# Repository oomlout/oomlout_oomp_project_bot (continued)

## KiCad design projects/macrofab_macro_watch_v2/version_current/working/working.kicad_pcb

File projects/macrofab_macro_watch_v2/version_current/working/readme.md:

# Macro_Watch_V2 by MacroFab  
This is a harvested standardized copy of a project from github.  
The original project can be found at:  
https://github.com/MacroFab/Macro_Watch_V2  
Please consult that link for additional, details, files, and license information.  
Note: It was auto harvested and if the original repo had more than one board file or anything out of the ordinary the files here are likely not representative.

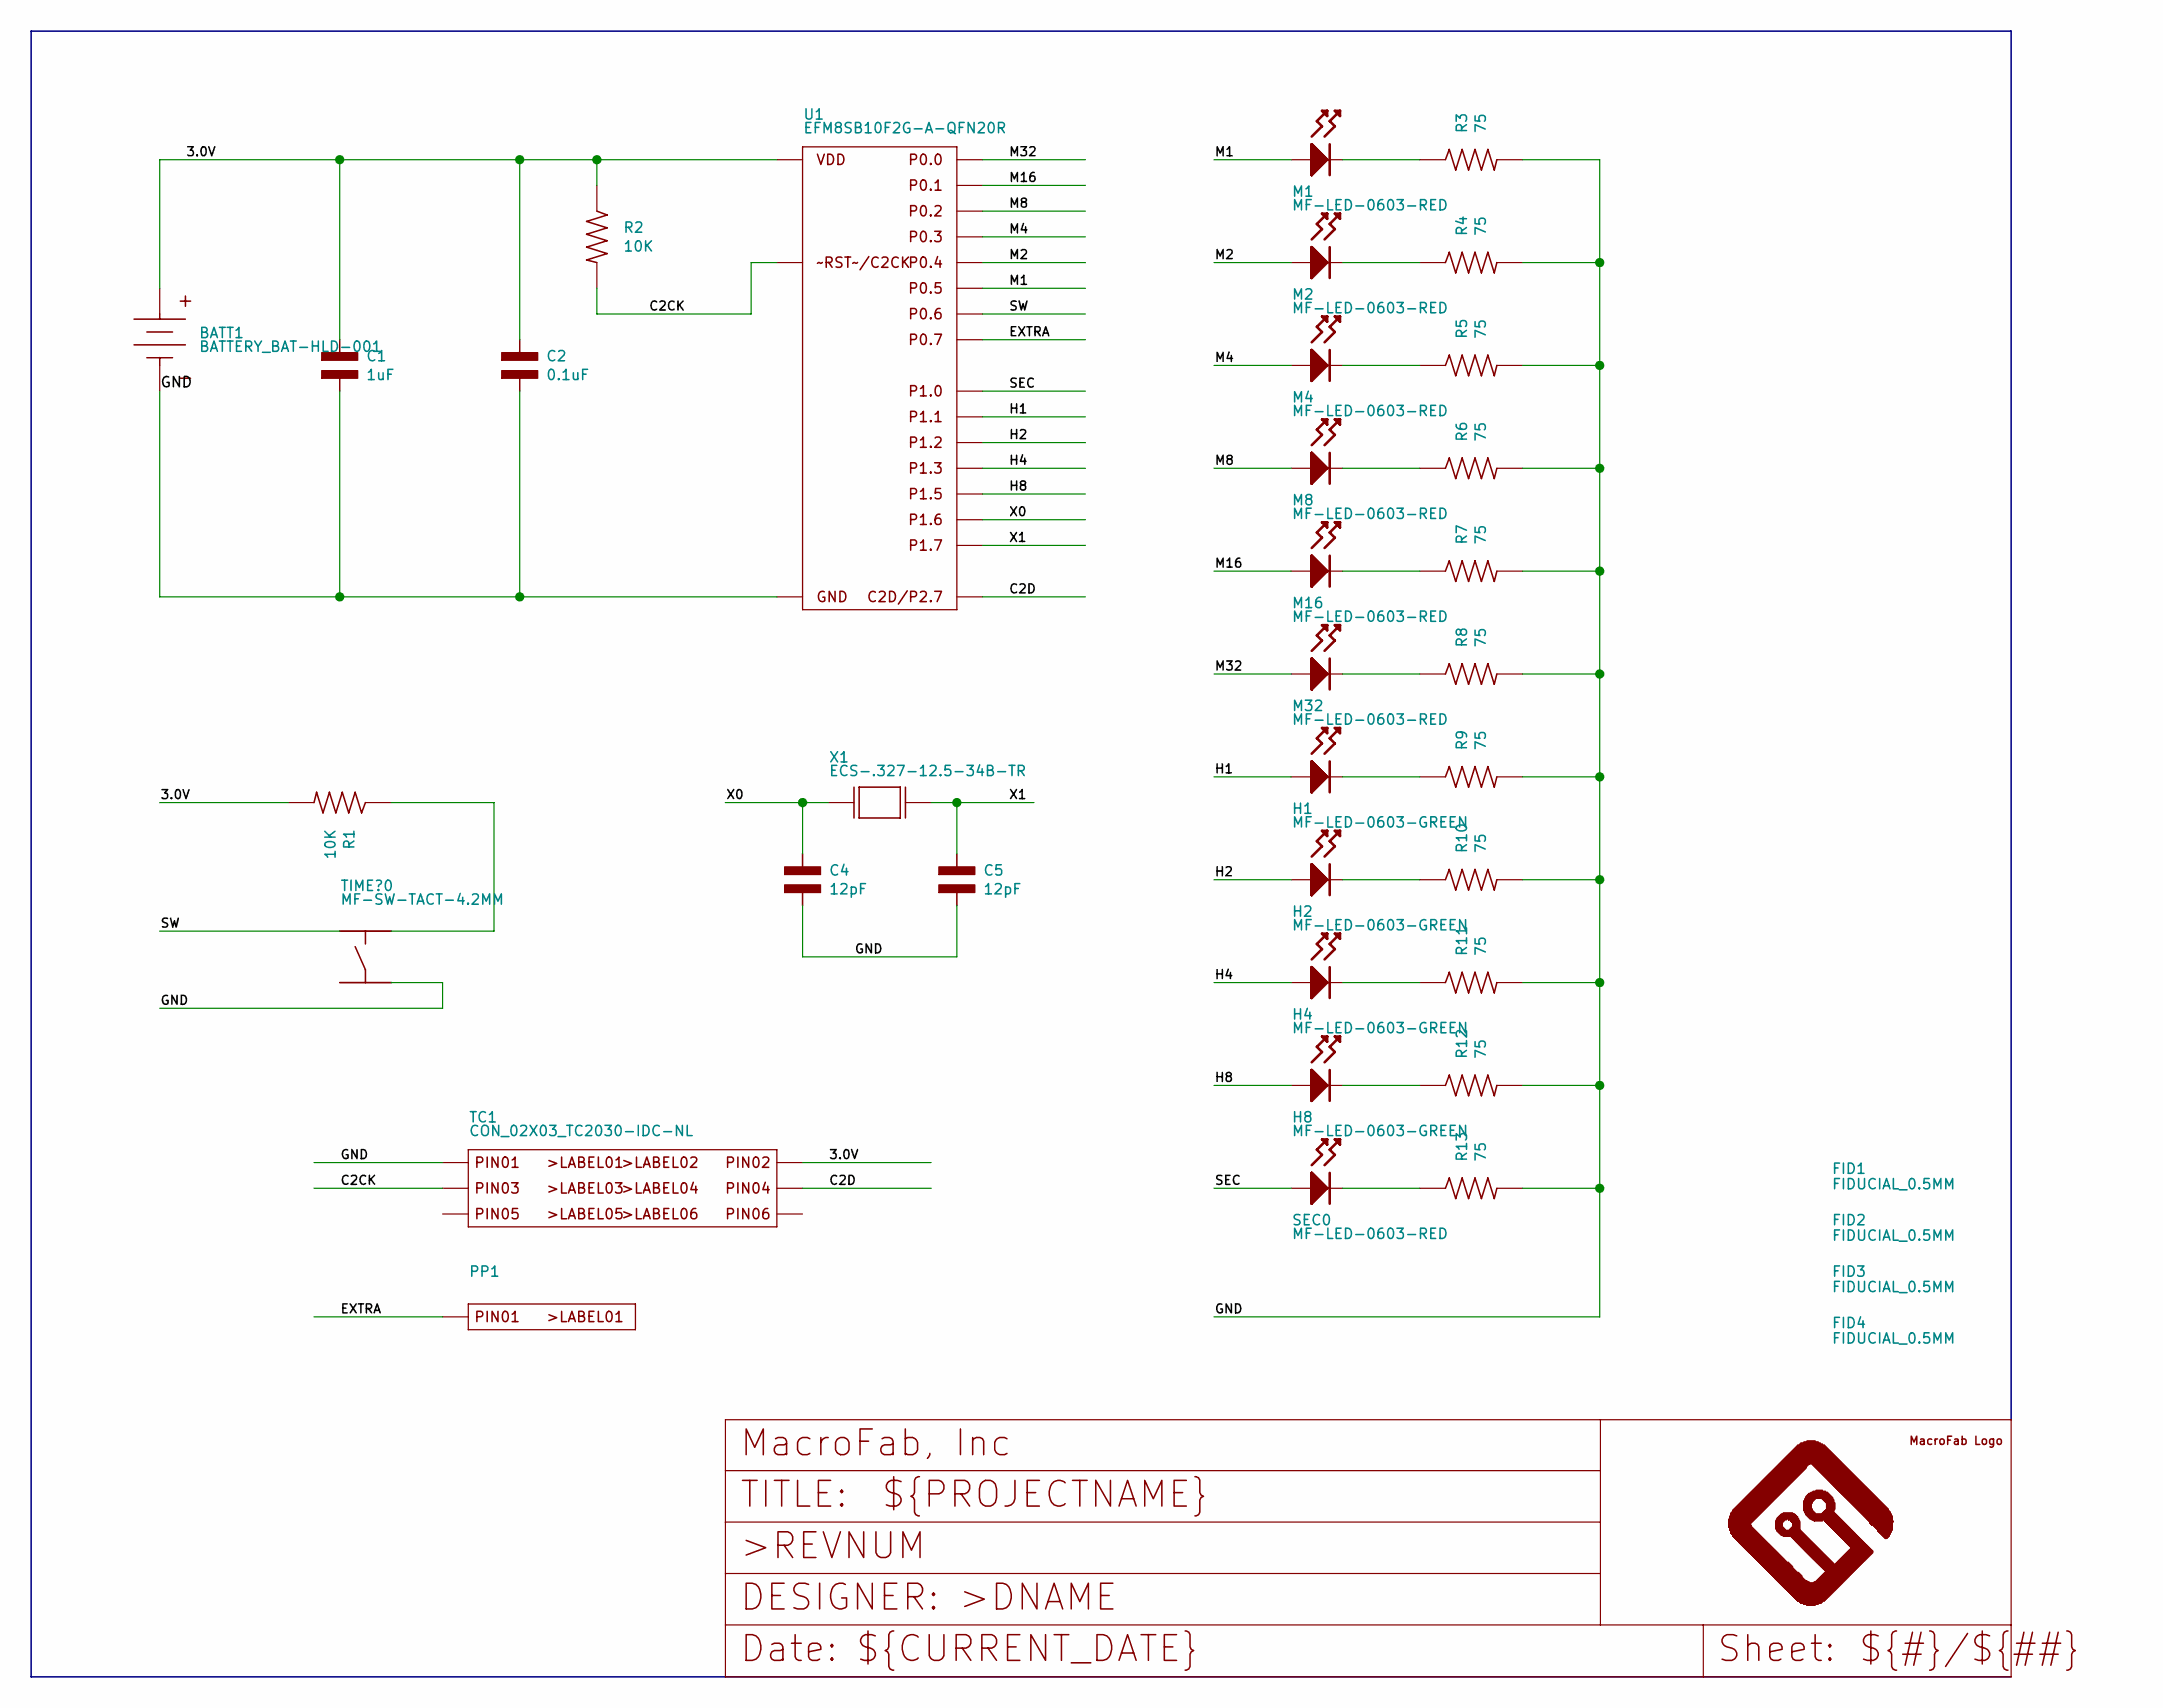
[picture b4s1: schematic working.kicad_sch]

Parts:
BATT1: BATTERY_BAT-HLD-001; BAT-HLD-001
C1: 1uF; C0402; MPN MF-CAP-0402-1uF
C2: 0.1uF; C0402; MPN MF-CAP-0402-0.1uF
C4, C5: 12pF; C0402; MPN 500R07S120KV4T
FID1, FID2, FID3, FID4: FIDUCIAL_0.5MM
FRAME1: MF_FRAMEDEFAULT; MF_FRAME_DEFAULT
H1, H2, H4, H8: MF-LED-0603-GREEN; LED0603
M1, M2, M4, M8, M16, M32: MF-LED-0603-RED; LED0603
PP1: POGO_PIN_01X01_70-9150; POGO_PIN_70-9150
R1, R2: 10K; R0402; MPN MF-RES-0402-10K
R3, R4, R5, R6, R7, R8, R9, R10, R11, R12, R13: 75; R0402; MPN MF-RES-0402-75
SEC0: MF-LED-0603-RED; LED0603
TC1: CON_02X03_TC2030-IDC-NL; TC2030-IDC-NL
TIME?0: MF-SW-TACT-4.2MM; TACT4.2MM
U1: EFM8SB10F2G-A-QFN20R; EFM8SB10F(2_4_8)G-A-QFN20; MPN EFM8SB10F2G-A-QFN20R
U$1: MF_LOGOLOGO_SMALL; MF_LOGO_SMALL
X1: ECS-.327-12.5-34B-TR; ECX-31B_SERIES; MPN ECS-.327-12.5-34B-TR

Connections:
3.0V: BATT1.POS_0 (POS), BATT1.POS_1 (POS), C1.P$1, C2.P$1, R1.P$2, R2.P$1, TC1.P$2 (PIN2), U1.P$4 (VDD)
C2CK: R2.P$2, TC1.P$3 (PIN3), U1.P$5 (~RST/C2CK)
C2D: TC1.P$4 (PIN4), U1.P$6 (C2D/P2.7)
EXTRA: PP1.P$1, U1.P$15 (P0.7)
GND: BATT1.NEG_0 (NEG), C1.P$2, C2.P$2, C4.P$2, C5.P$2, R3.P$2, R4.P$2, R5.P$2, R6.P$2, R7.P$2, R8.P$2, R9.P$2, R10.P$2, R11.P$2, R12.P$2, R13.P$2, TC1.P$1 (PIN1), TIME?0.P$4, U1.P$3 (GND), U1.P$12 (GND), U1.PAD (GND)
H1: H1.ANODE, U1.P$13 (P1.1)
H2: H2.ANODE, U1.P$11 (P1.2)
H4: H4.ANODE, U1.P$10 (P1.3)
H8: H8.ANODE, U1.P$9 (P1.5)
M1: M1.ANODE, U1.P$17 (P0.5)
M2: M2.ANODE, U1.P$18 (P0.4)
M4: M4.ANODE, U1.P$19 (P0.3)
M8: M8.ANODE, U1.P$20 (P0.2)
M16: M16.ANODE, U1.P$1 (P0.1)
M32: M32.ANODE, U1.P$2 (P0.0)
unnamed: R1.P$1, TIME?0.P$2
unnamed: M1.CATHODE, R3.P$1
unnamed: M2.CATHODE, R4.P$1
unnamed: M4.CATHODE, R5.P$1
unnamed: M8.CATHODE, R6.P$1
unnamed: M16.CATHODE, R7.P$1
unnamed: M32.CATHODE, R8.P$1
unnamed: H1.CATHODE, R9.P$1
unnamed: H2.CATHODE, R10.P$1
unnamed: H4.CATHODE, R11.P$1
unnamed: H8.CATHODE, R12.P$1
unnamed: R13.P$1, SEC0.CATHODE
SEC: SEC0.ANODE, U1.P$14 (P1.0)
SW: TIME?0.P$1, U1.P$16 (P0.6)
X0: C4.P$1, U1.P$8 (P1.6), X1.P$1 (X0)
X1: C5.P$1, U1.P$7 (P1.7), X1.P$2 (X1)

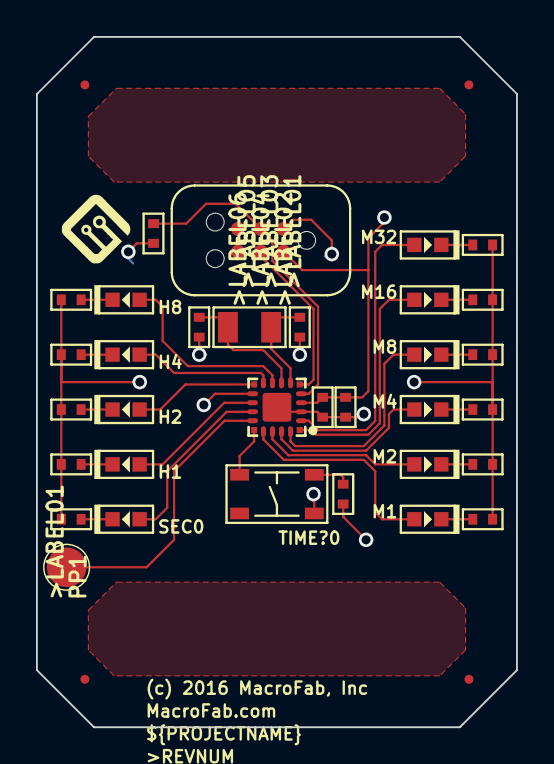
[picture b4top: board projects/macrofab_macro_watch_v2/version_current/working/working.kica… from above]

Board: 2 copper layers, 26.7 x 38.4 mm, 40 parts (1 on the bottom side), 31 nets.

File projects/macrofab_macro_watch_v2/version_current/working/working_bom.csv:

"Id";"Designator";"Footprint";"Quantity";"Designation";"Supplier and ref";
1;"U$1";"MF_LOGO_SMALL";1;"MF_LOGOLOGO_SMALL";;;
2;"R10,R11,R7,R12,R6,R8,R13,R5,R3,R9,R4";"R0402";11;"75";;;
3;"U1";"EFM8SB10F(2_4_8)G-A-QFN20";1;"EFM8SB10F2G-A-QFN20R";;;
4;"FRAME1";"MF_FRAME_DEFAULT";1;"";;;
5;"H8,H2,H4,H1";"LED0603";4;"MF-LED-0603-GREEN";;;
6;"C2";"C0402";1;"0.1uF";;;
7;"C1";"C0402";1;"1uF";;;
8;"M32,SEC0,M16,M8,M4,M1,M2";"LED0603";7;"MF-LED-0603-RED";;;
9;"FID1,FID3,FID2,FID4";"FIDUCIAL_0.5MM";4;"";;;
10;"R1,R2";"R0402";2;"10K";;;
11;"C4,C5";"C0402";2;"12pF";;;
12;"X1";"ECX-31B_SERIES";1;"ECS-.327-12.5-34B-TR";;;
13;"TC1";"TC2030-IDC-NL";1;"TC2030-IDC-NL";;;
14;"PP1";"POGO_PIN_70-9150";1;"";;;
15;"TIME?0";"TACT4.2MM";1;"MF-SW-TACT-4.2MM";;;
16;"BATT1";"BAT-HLD-001";1;"BAT-HLD-001";;;

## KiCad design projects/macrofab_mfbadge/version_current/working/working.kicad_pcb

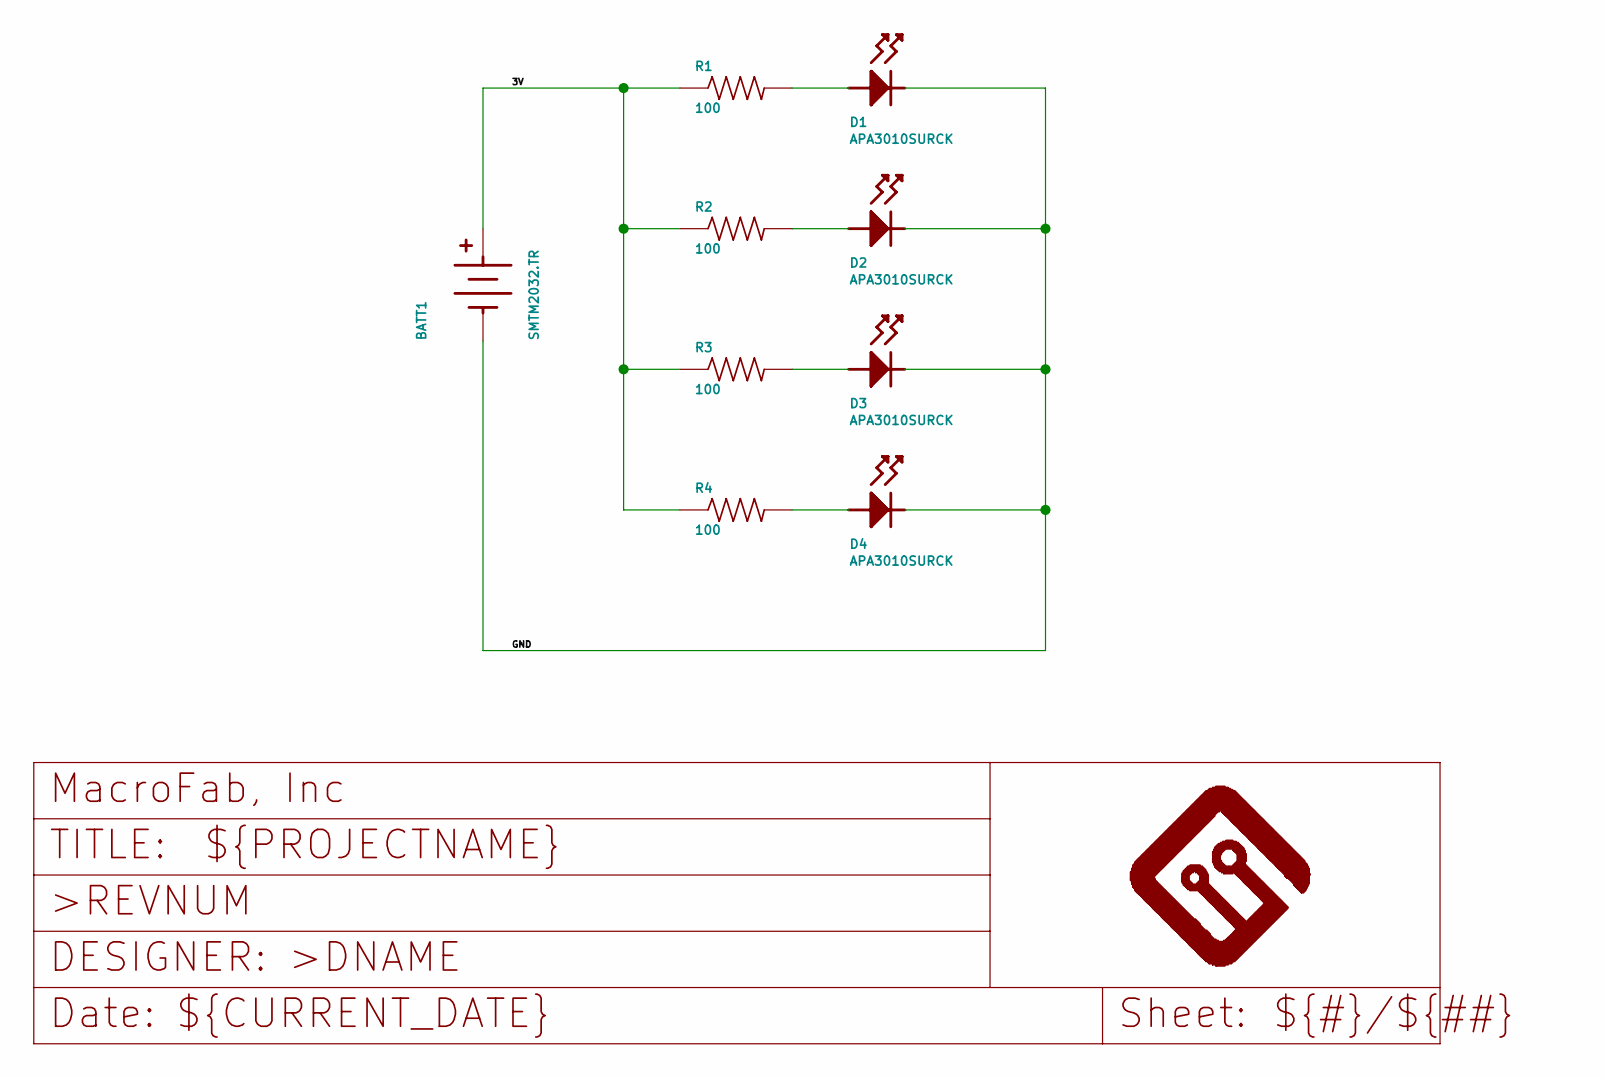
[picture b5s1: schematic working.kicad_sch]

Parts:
BATT1: SMTM2032.TR; SMTM2032
D1, D2, D3, D4: APA3010SURCK; APA3010
R1, R2, R3, R4: 100; 0805
U$1: MF_FRAMEMF_FRAME; MF_FRAME

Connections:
3V: BATT1.BATT- (-), D1.1 (CATHODE), D2.1 (CATHODE), D3.1 (CATHODE), D4.1 (CATHODE)
unnamed: D1.2 (ANODE), R1.2
unnamed: D2.2 (ANODE), R2.2
unnamed: D3.2 (ANODE), R3.2
unnamed: D4.2 (ANODE), R4.2
unnamed: BATT1.BATT+_0 (+), BATT1.BATT+_1 (+), R1.1, R2.1, R3.1, R4.1

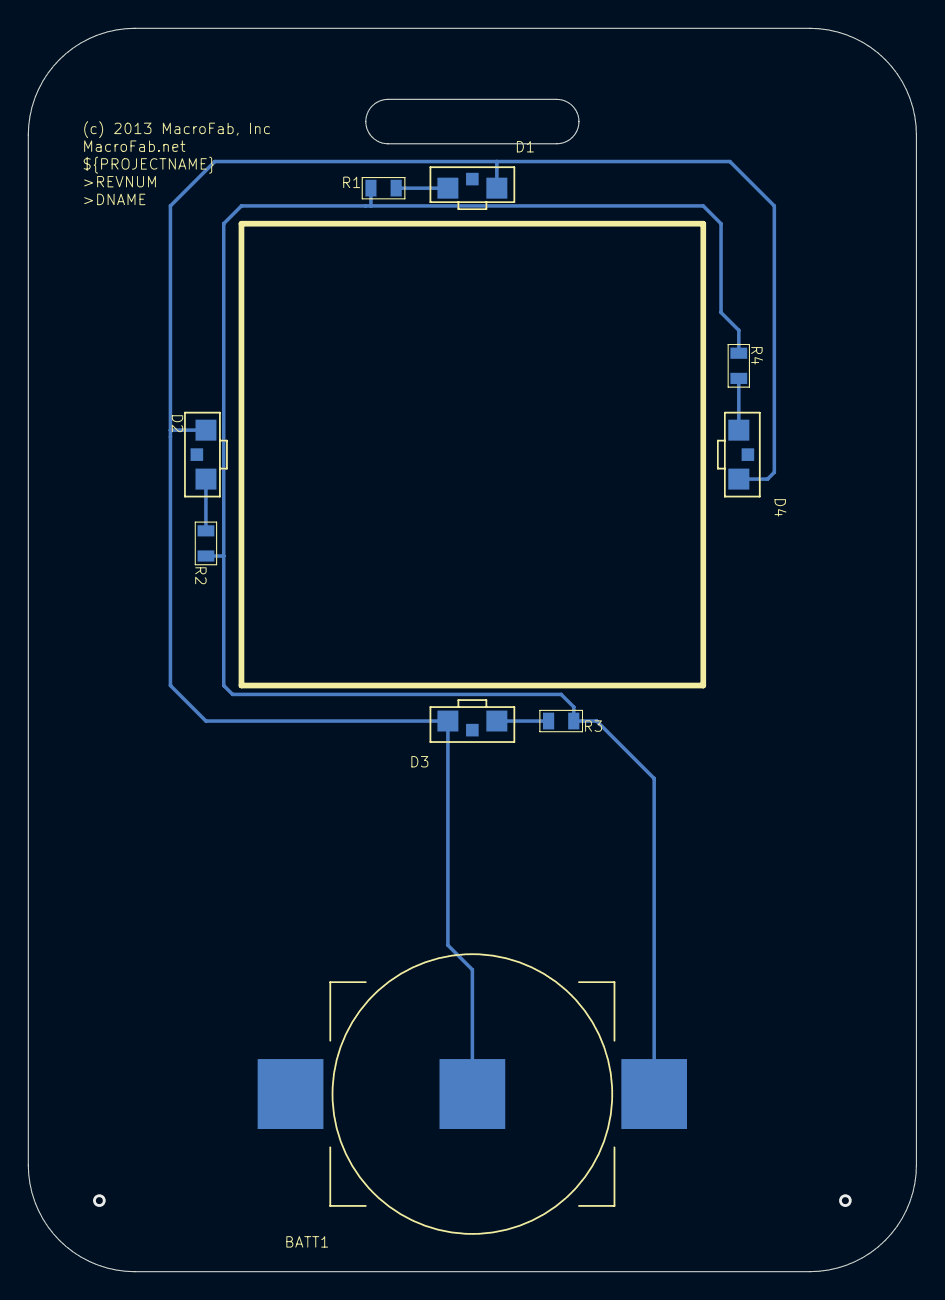
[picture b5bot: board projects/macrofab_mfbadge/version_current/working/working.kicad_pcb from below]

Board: 2 copper layers, 63.5 x 88.9 mm, 10 parts (10 on the bottom side), 6 nets.

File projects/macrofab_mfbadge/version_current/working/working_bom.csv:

"Id";"Designator";"Footprint";"Quantity";"Designation";"Supplier and ref";
1;"D2,D3,D1,D4";"APA3010";4;"APA3010SURCK";;;
2;"R1,R4,R3,R2";"0805";4;"100";;;
3;"U$1";"MF_FRAME";1;"MF_FRAMEMF_FRAME";;;
4;"BATT1";"SMTM2032";1;"SMTM2032.TR";;;

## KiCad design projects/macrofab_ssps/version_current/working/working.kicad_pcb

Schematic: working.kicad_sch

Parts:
C1, C6, C7, C8, C9, C10, C11, C24, C25, C26: 0.1uF; 0603
C2, C3, C4, C5: MF-CAP-6.3MM-100uF; 6.3MM_CAP_SMD
C12, C13: 47pF; C0603
C14, C15: 0.1uF; C0603
C16: 4.7uF; CP4MM
C17, C18, C19, C20, C21, C22, C23: .1uF; 0603
D1, D2, D3, D4, D5, D6: WP1043ID; WP1043
D7, D8, D9, D10, D11, D12: WP1043YD; WP1043
D13, D14, D15, D16, D17, D18, D19, D20, D21, D22, D23, D24, D25, D26, D27: WP1043GD; WP1043
DISP1, DISP2, DISP3, DISP4, DISP5: PSA08-11SRWA
EN1: PEL12T-4226F-S1024; PEL12T
FID1, FID2: FIDUCIAL_100MIL
FRAME1: MF_FRAMEDEFAULT; MF_FRAME_DEFAULT
GND0: 5001; KEYSTONE_5115-5119
J1: 61400413321
J2: CON_01X08_2.54MM_PIN_HEADER; 2.54MM_01X08_PIN_HEADER
L1: MI0603K300R-10; L0603
LCD1: CU16025-UW6J
R1, R2, R3, R4, R5, R6, R7, R15: 1K; 0603
R8, R9: 27; R0603
R10: 10K; R0603
R11: 4.7K; R0603
R12, R13, R14, R16, R17, R18, R19, R20, R21, R22: 10K; 0603
SW1, SW2: B3W-9000-RG2C; B3W-9000
SW3: 5501M112; 5501
U1: P8X32A-M44; P8X32A_QFN-44
U2, U3, U4, U5, U6, U9, U10, U14: STP16CP05XTTR; STP16CP05XTTR_TTSOP-24
U7: AP1084D25G-13; AP1084_TO-252-3L
U8: AP1084D33G-13; AP1084_TO-252-3L
U11: CAT24C512WI-GT3; SOIC-8_W
U12: IP4234CZ6; IP4234CZ6_SOT-457-6
U13: FT234XD-R; FT234X_DFN-12
UNK5V0: 5000; KEYSTONE_5115-5119
X1: ABMM-6.000MHZ-B2-T; 7MMX5MM

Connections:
2.5V: C3.POS, D1.A (ANODE), D2.A (ANODE), D3.A (ANODE), D4.A (ANODE), D5.A (ANODE), D6.A (ANODE), D7.A (ANODE), D8.A (ANODE), D9.A (ANODE), D10.A (ANODE), D11.A (ANODE), D12.A (ANODE), D13.A (ANODE), D14.A (ANODE), D15.A (ANODE), D16.A (ANODE), D17.A (ANODE), D18.A (ANODE), D19.A (ANODE), D20.A (ANODE), D21.A (ANODE), D22.A (ANODE), D23.A (ANODE), D24.A (ANODE), D25.A (ANODE), D26.A (ANODE), D27.A (ANODE), DISP1.P$11 (COM), DISP2.P$11 (COM), DISP3.P$11 (COM), DISP4.P$11 (COM), DISP5.P$11 (COM), SW1.ANODE_1, SW1.ANODE_2, SW2.ANODE_1, SW2.ANODE_2, SW3.ANODE_1, SW3.ANODE_2, U7.3 (OUT)
3.3V: C1.1, C5.POS, C6.1, C7.1, C8.1, C9.1, C10.1, C11.1, C15.P$1, C16.P$1, C17.2, C18.2, C19.2, C20.2, C22.2, C23.2, C24.1, EN1.5, R12.2, R13.2, R14.2, R16.2, R17.2, R20.1, R21.1, R22.1, U1.8 (VDD), U1.18 (VDD), U1.30 (VDD), U1.40 (VDD), U2.P$24 (VDD), U3.P$24 (VDD), U4.P$24 (VDD), U5.P$24 (VDD), U6.P$24 (VDD), U8.3 (OUT), U9.P$24 (VDD), U10.P$24 (VDD), U11.8 (VCC), U13.4 (VCC), U14.P$24 (VDD)
3V3OUT: C14.P$1, U13.2 (RESET#), U13.3 (3V3OUT), U13.9 (VCCIO)
D+_USB: J1.3 (D+), U12.1 (I/O1A)
D-_USB: J1.2 (D-), U12.6 (I/O2A)
DISP1_A: DISP1.P$1 (A), U2.P$20 (~OUT15)
DISP1_B: DISP1.P$18 (B), U2.P$5 (~OUT0)
DISP1_C: DISP1.P$16 (C), U2.P$7 (~OUT2)
DISP1_D: DISP1.P$13 (D), U2.P$10 (~OUT5)
DISP1_DATA: U1.2 (P5), U2.P$2 (SDI)
DISP1_DP: DISP1.P$12 (DP), U10.P$9 (~OUT4)
DISP1_E: DISP1.P$10 (E), U2.P$11 (~OUT6)
DISP1_F: DISP1.P$9 (F), U2.P$12 (~OUT7)
DISP1_G: DISP1.P$8 (G), U2.P$13 (~OUT8)
DISP1_H: DISP1.P$4 (H), U2.P$17 (~OUT12)
DISP1_K: DISP1.P$3 (K), U2.P$18 (~OUT13)
DISP1_M: DISP1.P$2 (M), U2.P$19 (~OUT14)
DISP1_N: DISP1.P$17 (N), U2.P$6 (~OUT1)
DISP1_P: DISP1.P$15, U2.P$8 (~OUT3)
DISP1_R: DISP1.P$14 (R), U2.P$9 (~OUT4)
DISP1_S: DISP1.P$6 (S), U2.P$15 (~OUT10)
DISP1_T: DISP1.P$7 (T), U2.P$14 (~OUT9)
DISP1_U: DISP1.P$5 (U), U2.P$16 (~OUT11)
DISP2_A: DISP2.P$1 (A), U3.P$20 (~OUT15)
DISP2_B: DISP2.P$18 (B), U3.P$5 (~OUT0)
DISP2_C: DISP2.P$16 (C), U3.P$7 (~OUT2)
DISP2_D: DISP2.P$13 (D), U3.P$10 (~OUT5)
DISP2_DATA: U2.P$22 (SDO), U3.P$2 (SDI)
DISP2_DP: DISP2.P$12 (DP), U10.P$8 (~OUT3)
DISP2_E: DISP2.P$10 (E), U3.P$11 (~OUT6)
DISP2_F: DISP2.P$9 (F), U3.P$12 (~OUT7)
DISP2_G: DISP2.P$8 (G), U3.P$13 (~OUT8)
DISP2_H: DISP2.P$4 (H), U3.P$17 (~OUT12)
DISP2_K: DISP2.P$3 (K), U3.P$18 (~OUT13)
DISP2_M: DISP2.P$2 (M), U3.P$19 (~OUT14)
DISP2_N: DISP2.P$17 (N), U3.P$6 (~OUT1)
DISP2_P: DISP2.P$15, U3.P$8 (~OUT3)
DISP2_R: DISP2.P$14 (R), U3.P$9 (~OUT4)
DISP2_S: DISP2.P$6 (S), U3.P$15 (~OUT10)
DISP2_T: DISP2.P$7 (T), U3.P$14 (~OUT9)
DISP2_U: DISP2.P$5 (U), U3.P$16 (~OUT11)
DISP3_A: DISP3.P$1 (A), U4.P$20 (~OUT15)
DISP3_B: DISP3.P$18 (B), U4.P$5 (~OUT0)
DISP3_C: DISP3.P$16 (C), U4.P$7 (~OUT2)
DISP3_D: DISP3.P$13 (D), U4.P$10 (~OUT5)
DISP3_DATA: U3.P$22 (SDO), U4.P$2 (SDI)
DISP3_DP: DISP3.P$12 (DP), U10.P$7 (~OUT2)
DISP3_E: DISP3.P$10 (E), U4.P$11 (~OUT6)
DISP3_F: DISP3.P$9 (F), U4.P$12 (~OUT7)
DISP3_G: DISP3.P$8 (G), U4.P$13 (~OUT8)
DISP3_H: DISP3.P$4 (H), U4.P$17 (~OUT12)
DISP3_K: DISP3.P$3 (K), U4.P$18 (~OUT13)
DISP3_M: DISP3.P$2 (M), U4.P$19 (~OUT14)
DISP3_N: DISP3.P$17 (N), U4.P$6 (~OUT1)
DISP3_P: DISP3.P$15, U4.P$8 (~OUT3)
DISP3_R: DISP3.P$14 (R), U4.P$9 (~OUT4)
DISP3_S: DISP3.P$6 (S), U4.P$15 (~OUT10)
DISP3_T: DISP3.P$7 (T), U4.P$14 (~OUT9)
DISP3_U: DISP3.P$5 (U), U4.P$16 (~OUT11)
DISP4_A: DISP4.P$1 (A), U5.P$20 (~OUT15)
DISP4_B: DISP4.P$18 (B), U5.P$5 (~OUT0)
DISP4_C: DISP4.P$16 (C), U5.P$7 (~OUT2)
DISP4_D: DISP4.P$13 (D), U5.P$10 (~OUT5)
DISP4_DATA: U4.P$22 (SDO), U5.P$2 (SDI)
DISP4_DP: DISP4.P$12 (DP), U10.P$6 (~OUT1)
DISP4_E: DISP4.P$10 (E), U5.P$11 (~OUT6)
DISP4_F: DISP4.P$9 (F), U5.P$12 (~OUT7)
DISP4_G: DISP4.P$8 (G), U5.P$13 (~OUT8)
DISP4_H: DISP4.P$4 (H), U5.P$17 (~OUT12)
DISP4_K: DISP4.P$3 (K), U5.P$18 (~OUT13)
DISP4_M: DISP4.P$2 (M), U5.P$19 (~OUT14)
DISP4_N: DISP4.P$17 (N), U5.P$6 (~OUT1)
DISP4_P: DISP4.P$15, U5.P$8 (~OUT3)
DISP4_R: DISP4.P$14 (R), U5.P$9 (~OUT4)
DISP4_S: DISP4.P$6 (S), U5.P$15 (~OUT10)
DISP4_T: DISP4.P$7 (T), U5.P$14 (~OUT9)
DISP4_U: DISP4.P$5 (U), U5.P$16 (~OUT11)
DISP5_A: DISP5.P$1 (A), U6.P$20 (~OUT15)
DISP5_B: DISP5.P$18 (B), U6.P$5 (~OUT0)
DISP5_C: DISP5.P$16 (C), U6.P$7 (~OUT2)
DISP5_D: DISP5.P$13 (D), U6.P$10 (~OUT5)
DISP5_DATA: U5.P$22 (SDO), U6.P$2 (SDI)
DISP5_DP: DISP5.P$12 (DP), U10.P$5 (~OUT0)
DISP5_E: DISP5.P$10 (E), U6.P$11 (~OUT6)
DISP5_F: DISP5.P$9 (F), U6.P$12 (~OUT7)
DISP5_G: DISP5.P$8 (G), U6.P$13 (~OUT8)
DISP5_H: DISP5.P$4 (H), U6.P$17 (~OUT12)
DISP5_K: DISP5.P$3 (K), U6.P$18 (~OUT13)
DISP5_M: DISP5.P$2 (M), U6.P$19 (~OUT14)
DISP5_N: DISP5.P$17 (N), U6.P$6 (~OUT1)
DISP5_P: DISP5.P$15, U6.P$8 (~OUT3)
DISP5_R: DISP5.P$14 (R), U6.P$9 (~OUT4)
DISP5_S: DISP5.P$6 (S), U6.P$15 (~OUT10)
DISP5_T: DISP5.P$7 (T), U6.P$14 (~OUT9)
DISP5_U: DISP5.P$5 (U), U6.P$16 (~OUT11)
DISP6_DATA: U6.P$22 (SDO), U9.P$2 (SDI)
DISP7_DATA: U9.P$22 (SDO), U10.P$2 (SDI)
DISP8_DATA: U10.P$22 (SDO), U14.P$2 (SDI)
DISP9_DATA: U14.P$22 (SDO)
DISPX_CLK: U1.44 (P3), U2.P$3 (CLK), U3.P$3 (CLK), U4.P$3 (CLK), U5.P$3 (CLK), U6.P$3 (CLK), U9.P$3 (CLK), U10.P$3 (CLK), U14.P$3 (CLK)
DISPX_LAT: U1.1 (P4), U2.P$4 (LE/DM1), U3.P$4 (LE/DM1), U4.P$4 (LE/DM1), U5.P$4 (LE/DM1), U6.P$4 (LE/DM1), U9.P$4 (LE/DM1), U10.P$4 (LE/DM1), U14.P$4 (LE/DM1)
ENCODER_A: C25.1, R18.2, U1.4 (P7)
ENCODER_B: C26.1, R19.1, U1.3 (P6)
GND: C1.2, C2.NEG, C3.NEG, C4.NEG, C5.NEG, C6.2, C7.2, C8.2, C9.2, C10.2, C11.2, C12.P$2, C13.P$2, C14.P$2, C15.P$2, C16.P$2, C17.1, C18.1, C19.1, C20.1, C22.1, C23.1, C24.2, C25.2, C26.2, EN1.C, GND0.P$1, J1.4 (GND), L1.P$2, LCD1.P$18 (GND2), R1.1, R2.1, R3.1, R4.1, R5.1, R6.1, R7.1, R10.P$1, R15.1, SW1.1, SW2.1, SW3.1A, U1.5 (VSS), U1.6 (~BOE), U1.17 (VSS), U1.27 (VSS), U1.39 (VSS), U2.P$1 (VSS/GND), U2.P$21 (~OE/DM2), U2.PAD (VSS/GND), U3.P$1 (VSS/GND), U3.P$21 (~OE/DM2), U3.PAD (VSS/GND), U4.P$1 (VSS/GND), U4.P$21 (~OE/DM2), U4.PAD (VSS/GND), U5.P$1 (VSS/GND), U5.P$21 (~OE/DM2), U5.PAD (VSS/GND), U6.P$1 (VSS/GND), U6.P$21 (~OE/DM2), U6.PAD (VSS/GND), U7.1 (GND), U8.1 (GND), U9.P$1 (VSS/GND), U9.P$21 (~OE/DM2), U9.PAD (VSS/GND), U10.P$1 (VSS/GND), U10.P$21 (~OE/DM2), U10.PAD (VSS/GND), U11.1 (A0), U11.2 (A1), U11.3 (A2), U11.4 (GND), U11.7 (WP), U12.2 (GND), U13.5 (GND), U13.P$1 (GND), U14.P$1 (VSS/GND), U14.P$21 (~OE/DM2), U14.PAD (VSS/GND), X1.P$2 (GND), X1.P$4 (GND)
LCD_SCK: LCD1.P$16 (SCK), U1.43 (P2)
LCD_SI/SO: LCD1.P$19 (SI/SO), U1.41 (P0)
LCD_STB: LCD1.P$17 (STB), U1.42 (P1)
unnamed: R1.2, U2.P$23 (R-EXT)
unnamed: R2.2, U3.P$23 (R-EXT)
unnamed: R3.2, U4.P$23 (R-EXT)
unnamed: R4.2, U5.P$23 (R-EXT)
unnamed: R5.2, U6.P$23 (R-EXT)
unnamed: R6.2, U9.P$23 (R-EXT)
unnamed: D16.C (CATHODE), U9.P$5 (~OUT0)
unnamed: D15.C (CATHODE), U9.P$6 (~OUT1)
unnamed: D14.C (CATHODE), U9.P$7 (~OUT2)
unnamed: D13.C (CATHODE), U9.P$8 (~OUT3)
unnamed: D12.C (CATHODE), U9.P$9 (~OUT4)
unnamed: D17.C (CATHODE), U10.P$20 (~OUT15)
unnamed: D10.C (CATHODE), U9.P$11 (~OUT6)
unnamed: D9.C (CATHODE), U9.P$12 (~OUT7)
unnamed: D8.C (CATHODE), U9.P$13 (~OUT8)
unnamed: D7.C (CATHODE), U9.P$14 (~OUT9)
unnamed: D6.C (CATHODE), U9.P$15 (~OUT10)
unnamed: D5.C (CATHODE), U9.P$16 (~OUT11)
unnamed: D4.C (CATHODE), U9.P$17 (~OUT12)
unnamed: D3.C (CATHODE), U9.P$18 (~OUT13)
unnamed: D2.C (CATHODE), U9.P$19 (~OUT14)
unnamed: D1.C (CATHODE), U9.P$20 (~OUT15)
unnamed: R7.2, U10.P$23 (R-EXT)
unnamed: D18.C (CATHODE), U10.P$19 (~OUT14)
unnamed: D19.C (CATHODE), U10.P$18 (~OUT13)
unnamed: D20.C (CATHODE), U10.P$17 (~OUT12)
unnamed: D21.C (CATHODE), U10.P$16 (~OUT11)
unnamed: D22.C (CATHODE), U10.P$15 (~OUT10)
unnamed: D23.C (CATHODE), U10.P$14 (~OUT9)
unnamed: D24.C (CATHODE), U10.P$13 (~OUT8)
unnamed: D25.C (CATHODE), U10.P$12 (~OUT7)
unnamed: D26.C (CATHODE), U10.P$11 (~OUT6)
unnamed: D27.C (CATHODE), U10.P$10 (~OUT5)
unnamed: R8.P$2, U13.1 (USBDM)
unnamed: D11.C (CATHODE), U9.P$10 (~OUT5)
unnamed: R9.P$2, U13.12 (USBDP)
unnamed: C12.P$1, R8.P$1, U12.4 (I/O2B)
unnamed: C13.P$1, R9.P$1, U12.3 (I/O1B)
unnamed: R15.2, U14.P$23 (R-EXT)
unnamed: EN1.1, U14.P$5 (~OUT0)
unnamed: EN1.2, U14.P$6 (~OUT1)
unnamed: EN1.4, U14.P$7 (~OUT2)
unnamed: SW1.CATHODE_1, U14.P$8 (~OUT3)
unnamed: SW1.CATHODE_2, U14.P$9 (~OUT4)
unnamed: SW2.CATHODE_1, U14.P$10 (~OUT5)
unnamed: SW2.CATHODE_2, U14.P$11 (~OUT6)
unnamed: SW3.CATHODE_1, U14.P$12 (~OUT7)
unnamed: SW3.CATHODE_2, U14.P$13 (~OUT8)
unnamed: R20.2, SW1.3
unnamed: R21.2, SW2.3
unnamed: R22.2, SW3.2
P11: J2.1, U1.12 (P11)
P12: J2.2, U1.13 (P12)
P13: J2.3, U1.14 (P13)
P14: J2.4, U1.15 (P14)
P15: J2.5, U1.16 (P15)
P16: J2.6, U1.19 (P16)
P17: J2.7, U1.20 (P17)
P18: J2.8, U1.21 (P18)
P19: U1.22 (P19)
P20: U1.23 (P20)
P21: U1.24 (P21)
P22: U1.25 (P22)
P23: U1.26 (P23)
P24: U1.31 (P24)
P25: U1.32 (P25)
P26: U1.33 (P26)
P27: U1.34 (P27)
RES: C21.1, R14.1, U1.7 (~RES)
RX: U1.37 (P30), U13.10 (RXD)
SCL: R12.1, U1.35 (P28), U11.6 (SCL)
SDA: R13.1, U1.36 (P29), U11.5 (SDA)
SHIELD: J1.S1 (SLD), J1.S2 (SLD), L1.P$1
SW_1: SW1.4, U1.9 (P8)
SW_2: SW2.4, U1.10 (P9)
SW_3: SW3.3, U1.11 (P10)
TERMINAL_A: EN1.A, R16.1, R18.1
TERMINAL_B: EN1.B, R17.1, R19.2
TX: U1.38 (P31), U13.7 (TXD)
USB_~RST: C21.2, U13.8 (RTS#)
VBUS_SENSE: R10.P$2, R11.P$1, U13.6 (CBUS0)
VIN: C2.POS, C4.POS, LCD1.P$20 (VCC2), U7.2 (IN), U8.2 (IN), UNK5V0.P$1
V_USB_0: J1.1 (5V), R11.P$2, U12.5 (VB)
X0: U1.29 (X0), X1.P$3 (X1)
X1: U1.28 (X1), X1.P$1 (X0)

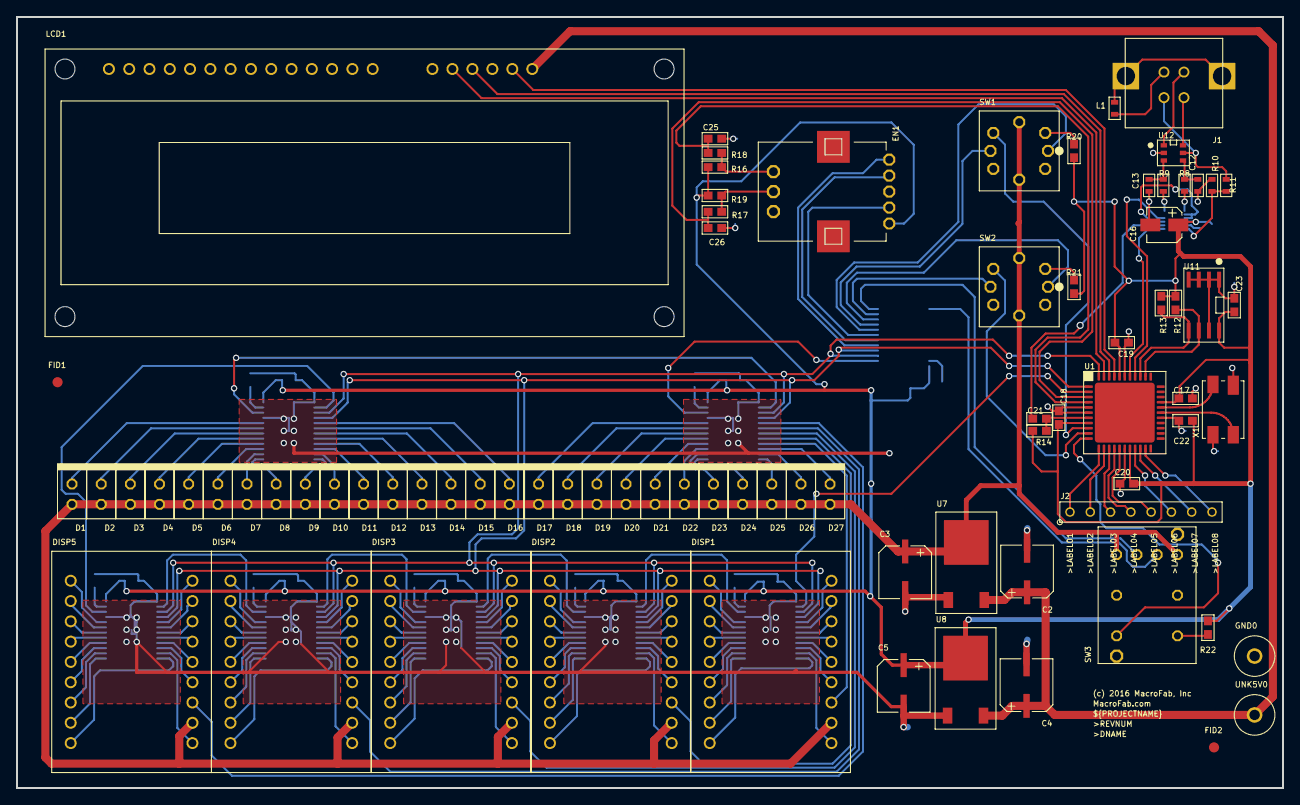
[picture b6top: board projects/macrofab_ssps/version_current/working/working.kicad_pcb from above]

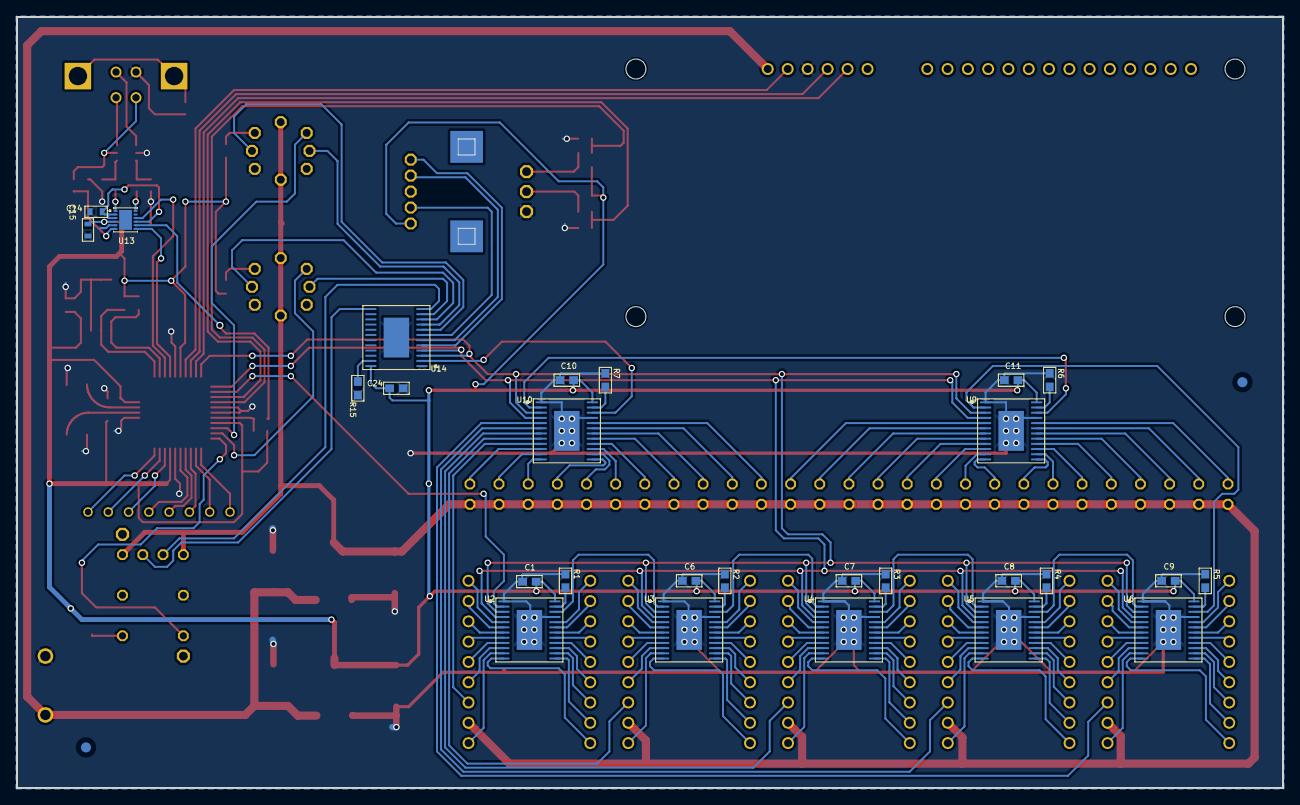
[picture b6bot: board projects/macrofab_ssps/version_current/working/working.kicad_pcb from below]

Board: 2 copper layers, 158.5 x 96.5 mm, 108 parts (27 on the bottom side), 182 nets.

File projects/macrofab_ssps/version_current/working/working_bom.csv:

"Id";"Designator";"Footprint";"Quantity";"Designation";"Supplier and ref";
1;"D19,D24,D21,D17,D22,D16,D20,D14,D15,D25,D18,D27,D26,D23,D13";"WP1043";15;"WP1043GD";;;
2;"C20,C23,C19,C17,C21,C18,C22";"0603";7;".1uF";;;
3;"D11,D7,D9,D12,D10,D8";"WP1043";6;"WP1043YD";;;
4;"C5,C3,C4,C2";"6.3MM_CAP_SMD";4;"MF-CAP-6.3MM-100uF";;;
5;"U12";"IP4234CZ6_SOT-457-6";1;"IP4234CZ6";;;
6;"GND0";"KEYSTONE_5115-5119";1;"5001";;;
7;"R19,R12,R13,R17,R21,R14,R18,R22,R16,R20";"0603";10;"10K";;;
8;"FRAME1";"MF_FRAME_DEFAULT";1;"MF_FRAMEDEFAULT";;;
9;"C13,C12";"C0603";2;"47pF";;;
10;"R8,R9";"R0603";2;"27";;;
11;"D4,D2,D6,D5,D3,D1";"WP1043";6;"WP1043ID";;;
12;"C16";"CP4MM";1;"4.7uF";;;
13;"SW3";"5501";1;"5501M112";;;
14;"U7";"AP1084_TO-252-3L";1;"AP1084D25G-13";;;
15;"DISP4,DISP2,DISP1,DISP5,DISP3";"PSA08-11SRWA";5;"PSA08-11SRWA";;;
16;"U1";"P8X32A_QFN-44";1;"P8X32A-M44";;;
17;"L1";"L0603";1;"MI0603K300R-10";;;
18;"R11";"R0603";1;"4.7K";;;
19;"SW2,SW1";"B3W-9000";2;"B3W-9000-RG2C";;;
20;"C26,C25,C11,C7,C1,C10,C8,C9,C24,C6";"0603";10;"0.1uF";;;
21;"J1";"61400413321";1;"61400413321";;;
22;"EN1";"PEL12T";1;"PEL12T-4226F-S1024";;;
23;"U11";"SOIC-8_W";1;"CAT24C512WI-GT3";;;
24;"LCD1";"CU16025-UW6J";1;"CU16025-UW6J";;;
25;"FID1,FID2";"FIDUCIAL_100MIL";2;"FIDUCIAL_100MIL";;;
26;"UNK5V0";"KEYSTONE_5115-5119";1;"5000";;;
27;"X1";"7MMX5MM";1;"ABMM-6.000MHZ-B2-T";;;
28;"R10";"R0603";1;"10K";;;
29;"U8";"AP1084_TO-252-3L";1;"AP1084D33G-13";;;
30;"J2";"2.54MM_01X08_PIN_HEADER";1;"";;;
31;"U3,U6,U14,U9,U4,U5,U10,U2";"STP16CP05XTTR_TTSOP-24";8;"STP16CP05XTTR";;;
32;"R3,R1,R2,R6,R15,R7,R5,R4";"0603";8;"1K";;;
33;"U13";"FT234X_DFN-12";1;"FT234XD-R";;;
34;"C14,C15";"C0603";2;"0.1uF";;;

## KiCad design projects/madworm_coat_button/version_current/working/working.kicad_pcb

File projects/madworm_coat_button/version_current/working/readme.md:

# Coat-Button by madworm  
This is a harvested standardized copy of a project from github.  
The original project can be found at:  
https://github.com/madworm/Coat-Button  
Please consult that link for additional, details, files, and license information.  
Note: It was auto harvested and if the original repo had more than one board file or anything out of the ordinary the files here are likely not representative.

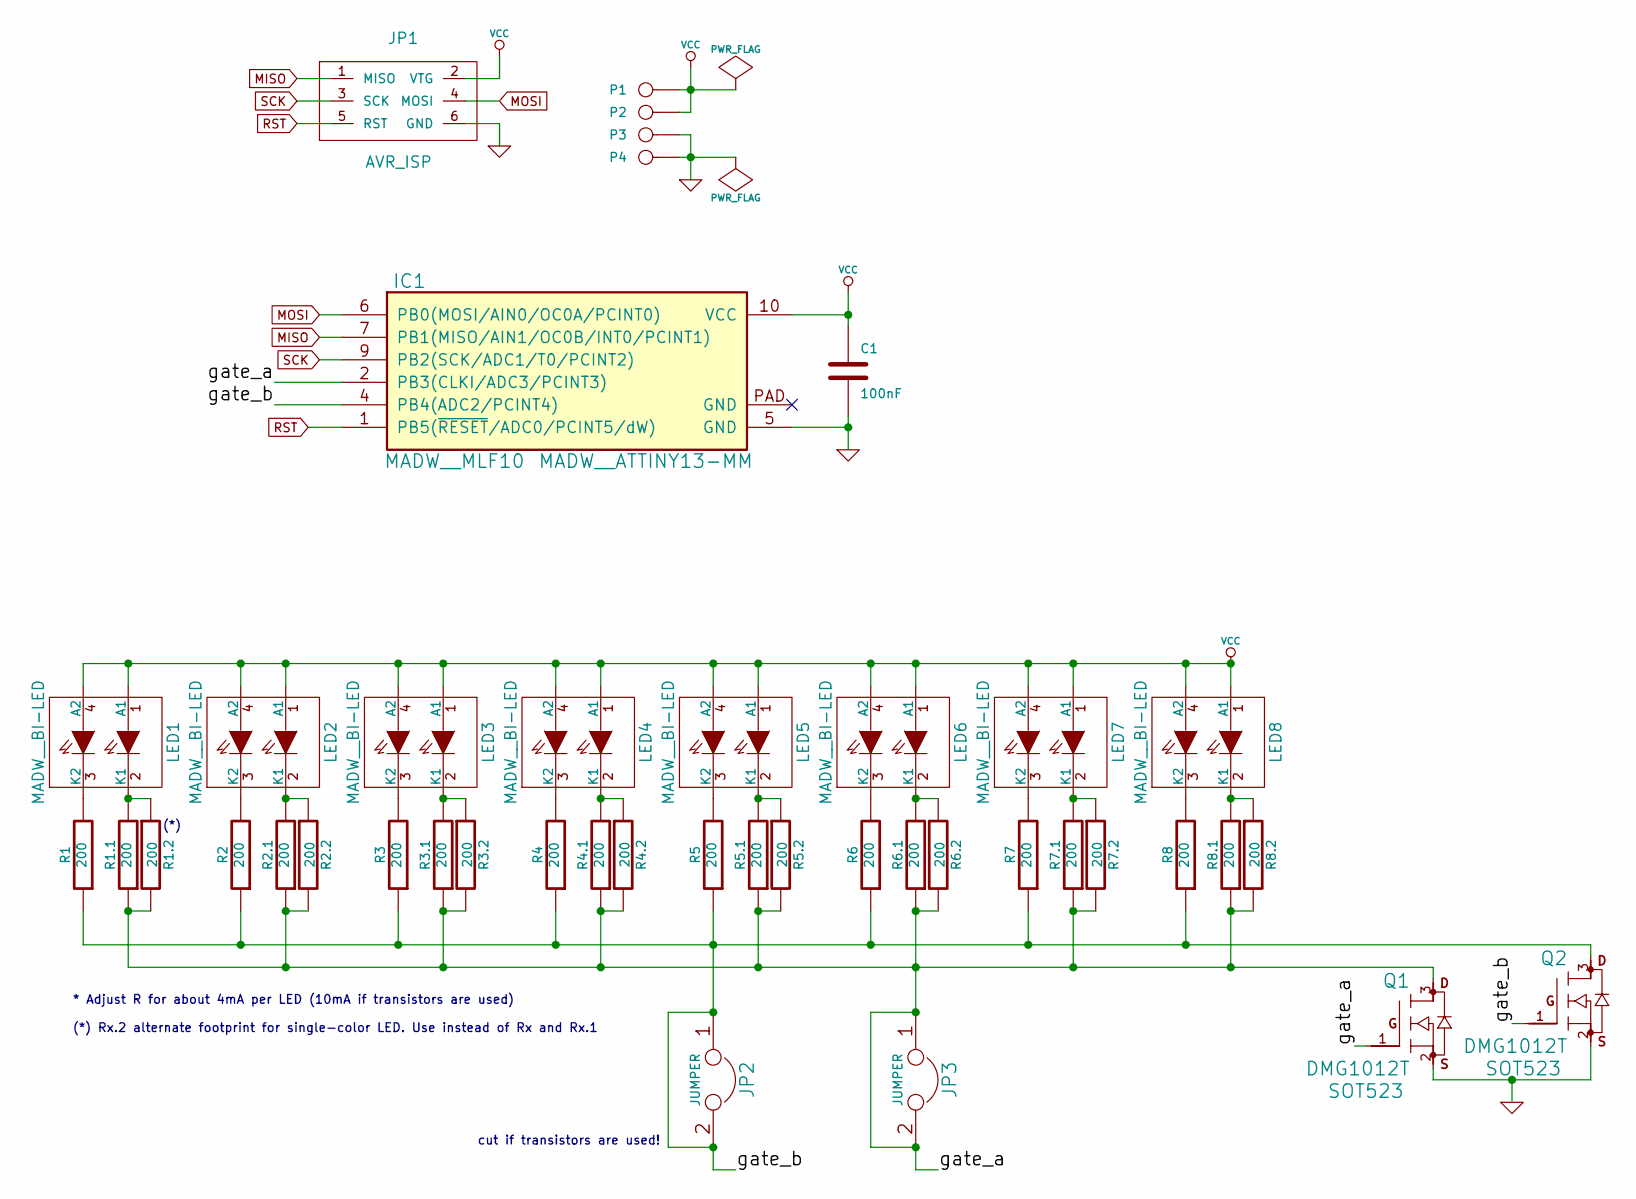
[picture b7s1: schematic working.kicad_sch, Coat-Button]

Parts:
C1: 100nF
IC1: MADW__ATTINY13-MM; MADW__MLF10
JP1: AVR_ISP
JP2, JP3: JUMPER
LED1, LED2, LED3, LED4, LED5, LED6, LED7, LED8: MADW__BI-LED
P1, P2, P3, P4: CONN_1
Q1, Q2: DMG1012T; SOT523
R1, R1.1, R1.2, R2, R2.1, R2.2, R3, R3.1, R3.2, R4, R4.1, R4.2, R5, R5.1, R5.2, R6, R6.1, R6.2, R7, R7.1, R7.2, R8, R8.1, R8.2: 200

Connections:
/gate_a: IC1.2 (PB3(CLKI/ADC3/PCINT3)), JP3.1, JP3.2, Q1.1 (G), Q1.3 (D), R1.1.1, R1.2.2, R2.1.1, R2.2.2, R3.1.1, R3.2.2, R4.1.1, R4.2.2, R5.1.1, R5.2.2, R6.1.1, R6.2.2, R7.1.1, R7.2.2, R8.1.1, R8.2.2
/gate_b: IC1.4 (PB4(ADC2/PCINT4)), JP2.1, JP2.2, Q2.1 (G), Q2.3 (D), R1.1, R2.1, R3.1, R4.1, R5.1, R6.1, R7.1, R8.1
GND: C1.2, IC1.5 (GND), JP1.6 (GND), P3.1, P4.1, Q1.2 (S), Q2.2 (S)
MISO: IC1.7 (PB1(MISO/AIN1/OC0B/INT0/PCINT1)), JP1.1 (MISO)
MOSI: IC1.6 (PB0(MOSI/AIN0/OC0A/PCINT0)), JP1.4 (MOSI)
unnamed: LED1.2 (K1), R1.1.2, R1.2.1
unnamed: LED1.3 (K2), R1.2
unnamed: LED2.2 (K1), R2.1.2, R2.2.1
unnamed: LED2.3 (K2), R2.2
unnamed: LED3.2 (K1), R3.1.2, R3.2.1
unnamed: LED3.3 (K2), R3.2
unnamed: LED4.2 (K1), R4.1.2, R4.2.1
unnamed: LED4.3 (K2), R4.2
unnamed: LED5.2 (K1), R5.1.2, R5.2.1
unnamed: LED5.3 (K2), R5.2
unnamed: LED6.2 (K1), R6.1.2, R6.2.1
unnamed: LED6.3 (K2), R6.2
unnamed: LED7.2 (K1), R7.1.2, R7.2.1
unnamed: LED7.3 (K2), R7.2
unnamed: LED8.2 (K1), R8.1.2, R8.2.1
unnamed: LED8.3 (K2), R8.2
RST: IC1.1 (PB5(~RESET/ADC0/PCINT5/dW)), JP1.5 (RST)
SCK: IC1.9 (PB2(SCK/ADC1/T0/PCINT2)), JP1.3 (SCK)
VCC: C1.1, IC1.10 (VCC), JP1.2 (VTG), LED1.1 (A1), LED1.4 (A2), LED2.1 (A1), LED2.4 (A2), LED3.1 (A1), LED3.4 (A2), LED4.1 (A1), LED4.4 (A2), LED5.1 (A1), LED5.4 (A2), LED6.1 (A1), LED6.4 (A2), LED7.1 (A1), LED7.4 (A2), LED8.1 (A1), LED8.4 (A2), P1.1, P2.1

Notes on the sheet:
(*)
* Adjust R for about 4mA per LED (10mA if transistors are used) (*) Rx.2 alternate footprint for single-color LED. Use instead of Rx and Rx.1
cut if transistors are used!

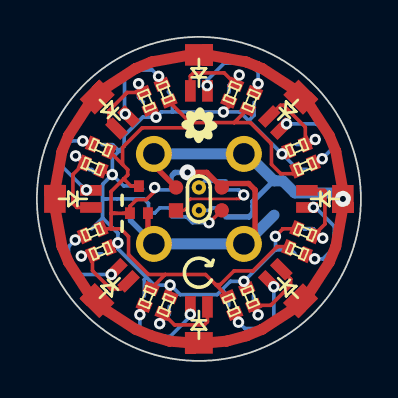
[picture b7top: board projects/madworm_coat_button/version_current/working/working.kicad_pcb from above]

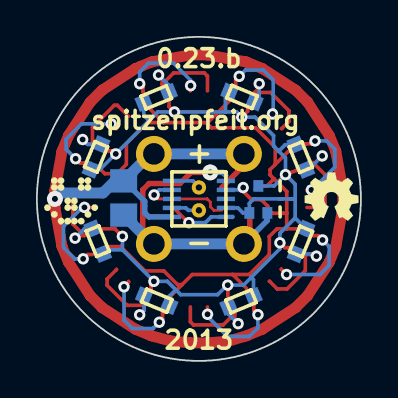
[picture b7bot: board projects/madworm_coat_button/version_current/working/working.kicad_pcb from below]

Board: 2 copper layers, 18.0 x 18.0 mm, 46 parts (14 on the bottom side), 24 nets.

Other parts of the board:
G1: OSHW-logo_silkscreen_3mm
G2: LED_smile_silkscreen_3mm
G3: floral-shape_silkscreen_2mm
